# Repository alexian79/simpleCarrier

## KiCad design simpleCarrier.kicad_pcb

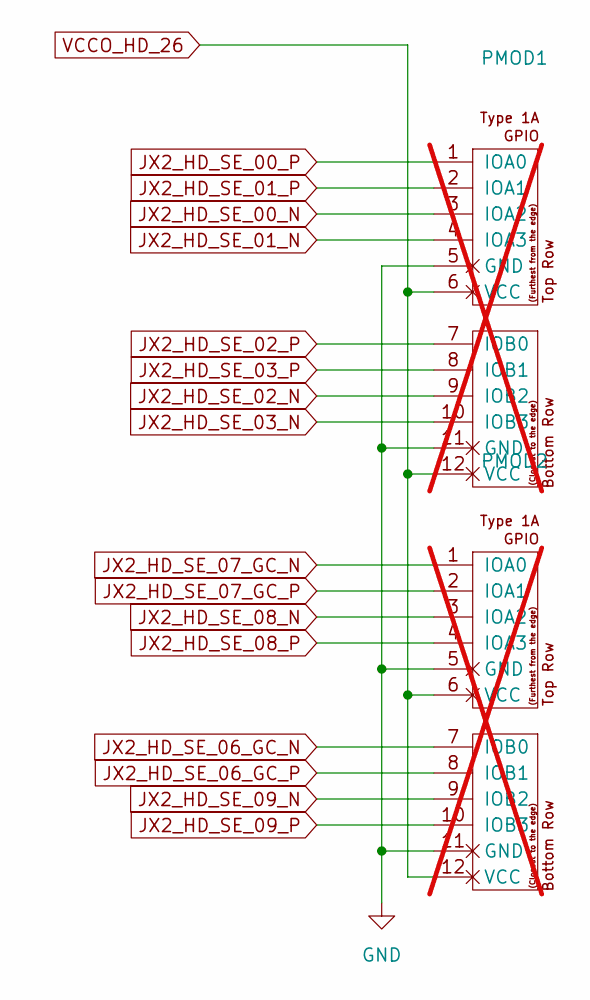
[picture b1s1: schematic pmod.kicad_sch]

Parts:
PMOD1, PMOD2: PMOD-Device-x2-Type-1A-GPIO; pmod_pin_array_6x2; not fitted

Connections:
GND: PMOD1.5 (GND), PMOD1.11 (GND), PMOD2.5 (GND), PMOD2.11 (GND); also elsewhere on the board
JX2_HD_SE_00_N: PMOD1.3 (IOA2); also elsewhere on the board
JX2_HD_SE_00_P: PMOD1.1 (IOA0); also elsewhere on the board
JX2_HD_SE_01_N: PMOD1.4 (IOA3); also elsewhere on the board
JX2_HD_SE_01_P: PMOD1.2 (IOA1); also elsewhere on the board
JX2_HD_SE_02_N: PMOD1.9 (IOB2); also elsewhere on the board
JX2_HD_SE_02_P: PMOD1.7 (IOB0); also elsewhere on the board
JX2_HD_SE_03_N: PMOD1.10 (IOB3); also elsewhere on the board
JX2_HD_SE_03_P: PMOD1.8 (IOB1); also elsewhere on the board
JX2_HD_SE_06_GC_N: PMOD2.7 (IOB0); also elsewhere on the board
JX2_HD_SE_06_GC_P: PMOD2.8 (IOB1); also elsewhere on the board
JX2_HD_SE_07_GC_N: PMOD2.1 (IOA0); also elsewhere on the board
JX2_HD_SE_07_GC_P: PMOD2.2 (IOA1); also elsewhere on the board
JX2_HD_SE_08_N: PMOD2.3 (IOA2); also elsewhere on the board
JX2_HD_SE_08_P: PMOD2.4 (IOA3); also elsewhere on the board
JX2_HD_SE_09_N: PMOD2.9 (IOB2); also elsewhere on the board
JX2_HD_SE_09_P: PMOD2.10 (IOB3); also elsewhere on the board
VCCO_HD_26: PMOD1.6 (VCC), PMOD1.12 (VCC), PMOD2.6 (VCC), PMOD2.12 (VCC); also elsewhere on the board

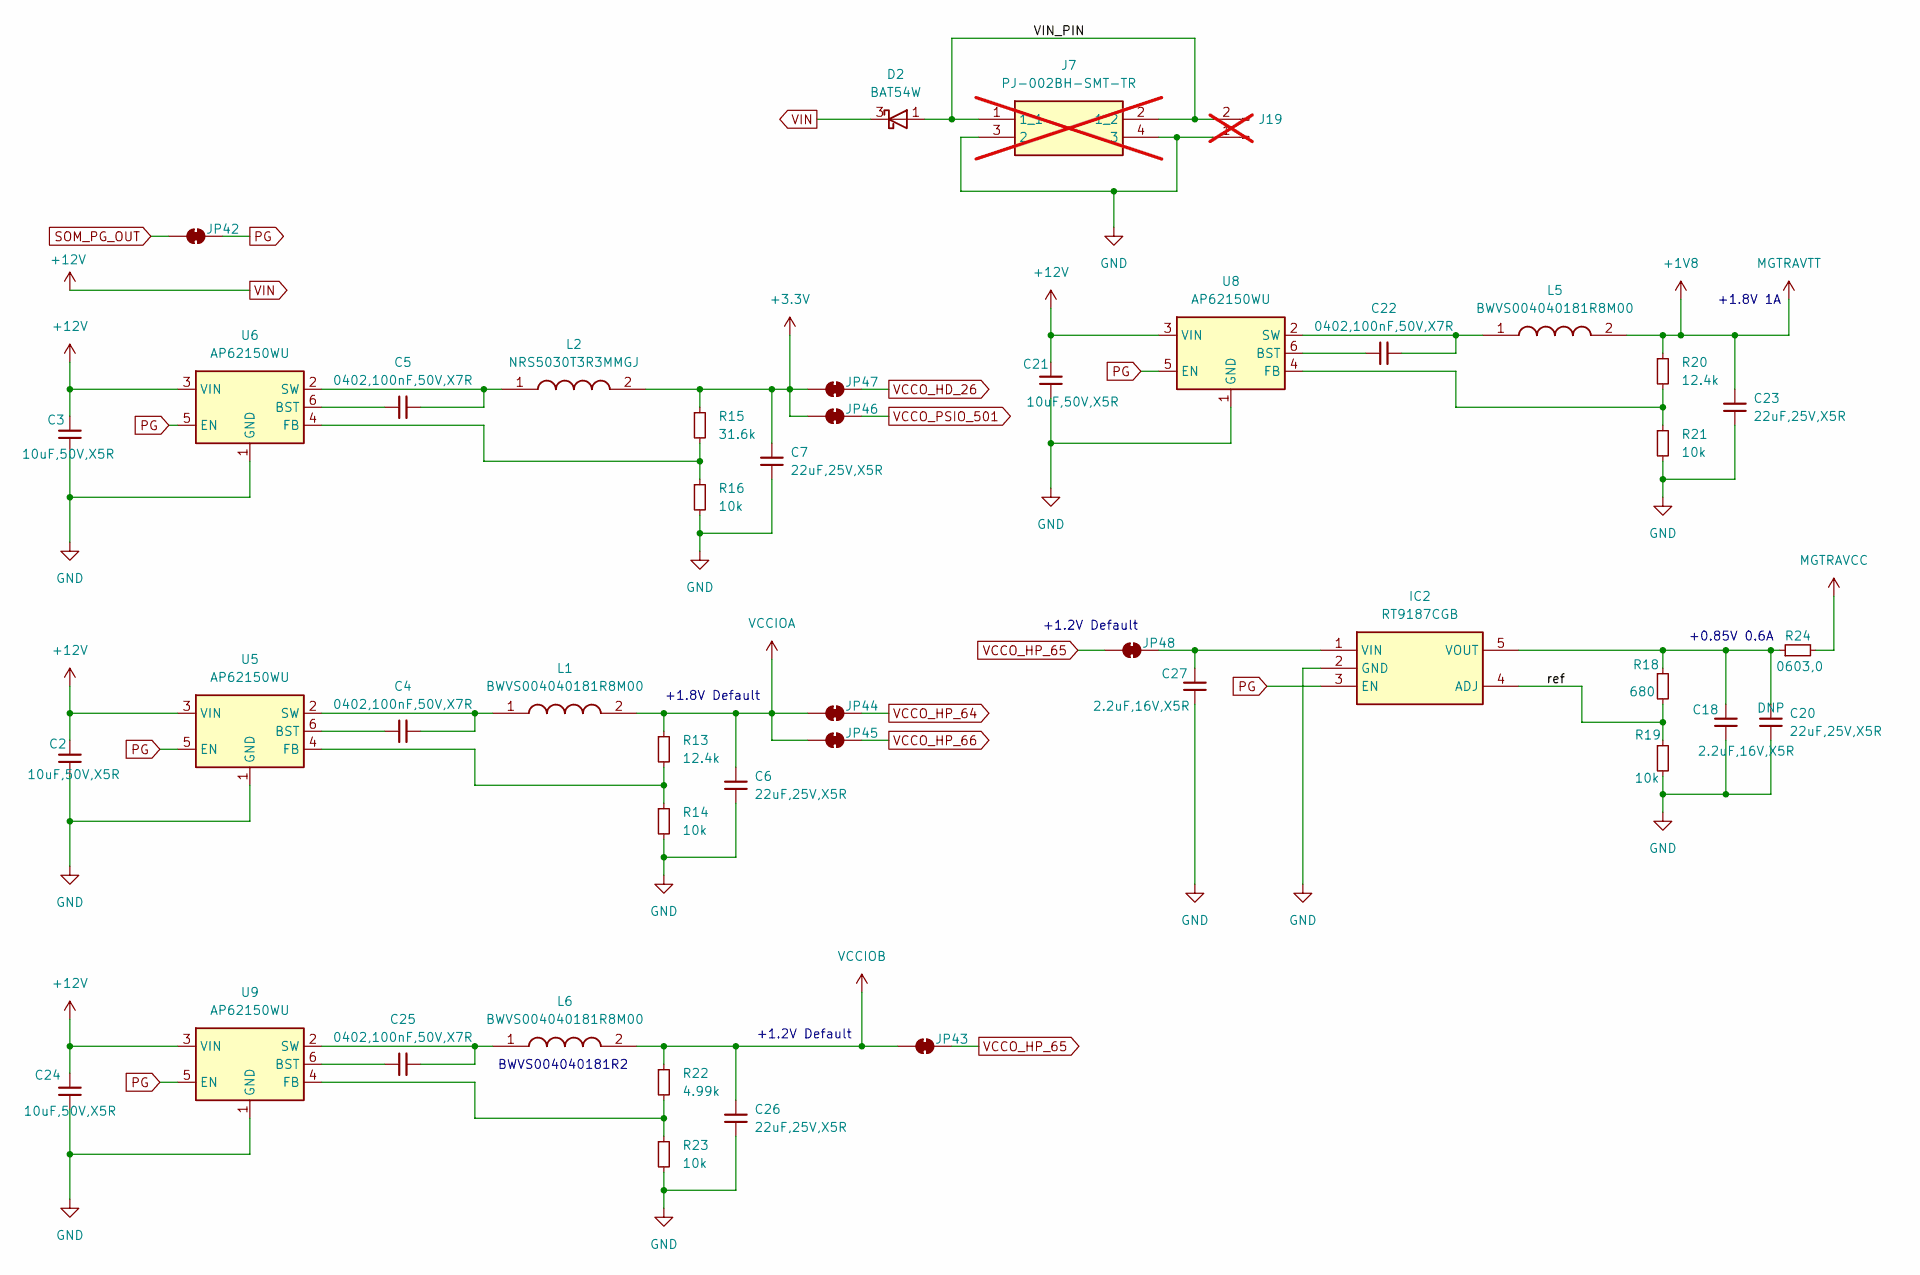
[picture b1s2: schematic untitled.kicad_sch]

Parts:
C2, C3, C21, C24: 10uF,50V,X5R; C_0805_2012Metric; MFGPN GRM21BR61H106KE43L; LCSC C440198
C4, C5, C22, C25: 0402,100nF,50V,X7R; C_0402_1005Metric; MFGPN CL05B104KB54PNC; LCSC C307331
C6, C7, C20, C23, C26: 22uF,25V,X5R; C_0805_2012Metric; MFGPN CL21A226MAQNNNE; LCSC C45783
C18, C27: 2.2uF,16V,X5R; C_0603_1608Metric; MFGPN CL10A225KO8NNNC; LCSC C23630
D2: BAT54W; SOT-323_SC-70
IC2: RT9187CGB; SOT94P279X130-5N; Manufacturer_Part_Number RT9187CGB
J7: PJ-002BH-SMT-TR; PJ002BHSMTTR; Manufacturer_Part_Number PJ-002BH-SMT-TR; Mouser Part Number 490-PJ-002BH-SMT-TR; not fitted
J19: Conn_01x02_Pin; PinHeader_1x02_P2.54mm_Vertical; not fitted
JP42, JP43, JP44, JP45, JP46, JP47, JP48: SolderJumper_2_Bridged; SolderJumper-2_P1.3mm_Bridged_RoundedPad1.0x1.5mm
L1, L5, L6: BWVS004040181R8M00; Manufacturer_Part_Number BWVS004040181R8M00
L2: NRS5030T3R3MMGJ; INDC4949X330N; Manufacturer_Part_Number NRS5030T3R3MMGJ; Mouser Part Number 963-NRS5030T3R3MMGJ
R13, R20: 12.4k; R_0603_1608Metric; MFGPN 0603WAF1202T5E; LCSC C22790
R14, R16, R19, R21, R23: 10k; R_0603_1608Metric; MFGPN 0603WAF1002T5E; LCSC C25804
R15: 31.6k; R_0603_1608Metric; MFGPN 0603WAF3002T5E; LCSC C22984
R18: 680; R_0603_1608Metric; MFGPN 0603WAF6800T5E; LCSC C23228
R22: 4.99k; R_0603_1608Metric; MFGPN 0603WAF1202T5E; LCSC C23046
R24: 0603,0; R_0603_1608Metric; MFGPN 0603WAF0000T5E; LCSC C21189
U5, U6, U8, U9: AP62150WU; TSOT-23-6

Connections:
+1V8: C23.1, L5.2, R20.1; also elsewhere on the board
+3.3V: C7.1, JP46.1 (A), JP47.1 (A), L2.2, R15.1; also elsewhere on the board
/power/VIN_PIN: D2.1 (A), J7.1 (1_1), J7.2 (1_2), J19.2
/power/ref: IC2.4 (ADJ), R18.2, R19.1
GND: C2.2, C3.2, C6.2, C7.2, C18.2, C20.2, C21.2, C23.2, C24.2, C26.2, C27.2, IC2.2 (GND), J7.3 (2), J7.4 (3), J19.1, R14.2, R16.2, R19.2, R21.2, R23.2, U5.1 (GND), U6.1 (GND), U8.1 (GND), U9.1 (GND); also elsewhere on the board
MGTRAVCC: R24.2; also elsewhere on the board
unnamed: C27.1, IC2.1 (VIN), JP48.2 (B)
unnamed: C18.1, C20.1, IC2.5 (VOUT), R18.1, R24.1
unnamed: C4.1, U5.6 (BST)
unnamed: R13.2, R14.1, U5.4 (FB)
unnamed: C4.2, L1.1, U5.2 (SW)
unnamed: C5.1, U6.6 (BST)
unnamed: R15.2, R16.1, U6.4 (FB)
unnamed: C5.2, L2.1, U6.2 (SW)
unnamed: C22.1, U8.6 (BST)
unnamed: R20.2, R21.1, U8.4 (FB)
unnamed: C22.2, L5.1, U8.2 (SW)
unnamed: C25.1, U9.6 (BST)
unnamed: R22.2, R23.1, U9.4 (FB)
unnamed: C25.2, L6.1, U9.2 (SW)
PG: IC2.3 (EN), JP42.2 (B), U5.5 (EN), U6.5 (EN), U8.5 (EN), U9.5 (EN)
SOM_PG_OUT: JP42.1 (A); also elsewhere on the board
VCCIOA: C6.1, JP44.1 (A), JP45.1 (A), L1.2, R13.1
VCCIOB: C26.1, JP43.1 (A), L6.2, R22.1
VCCO_HD_26: JP47.2 (B); also elsewhere on the board
VCCO_HP_64: JP44.2 (B); also elsewhere on the board
VCCO_HP_65: JP43.2 (B), JP48.1 (A); also elsewhere on the board
VCCO_HP_66: JP45.2 (B); also elsewhere on the board
VCCO_PSIO_501: JP46.2 (B); also elsewhere on the board
VIN: C2.1, C3.1, C21.1, C24.1, D2.3 (K), U5.3 (VIN), U6.3 (VIN), U8.3 (VIN), U9.3 (VIN); also elsewhere on the board

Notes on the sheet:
+1.8V Default
+1.8V 1A
+1.2V Default
BWVS004040181R2
+0.85V 0.6A

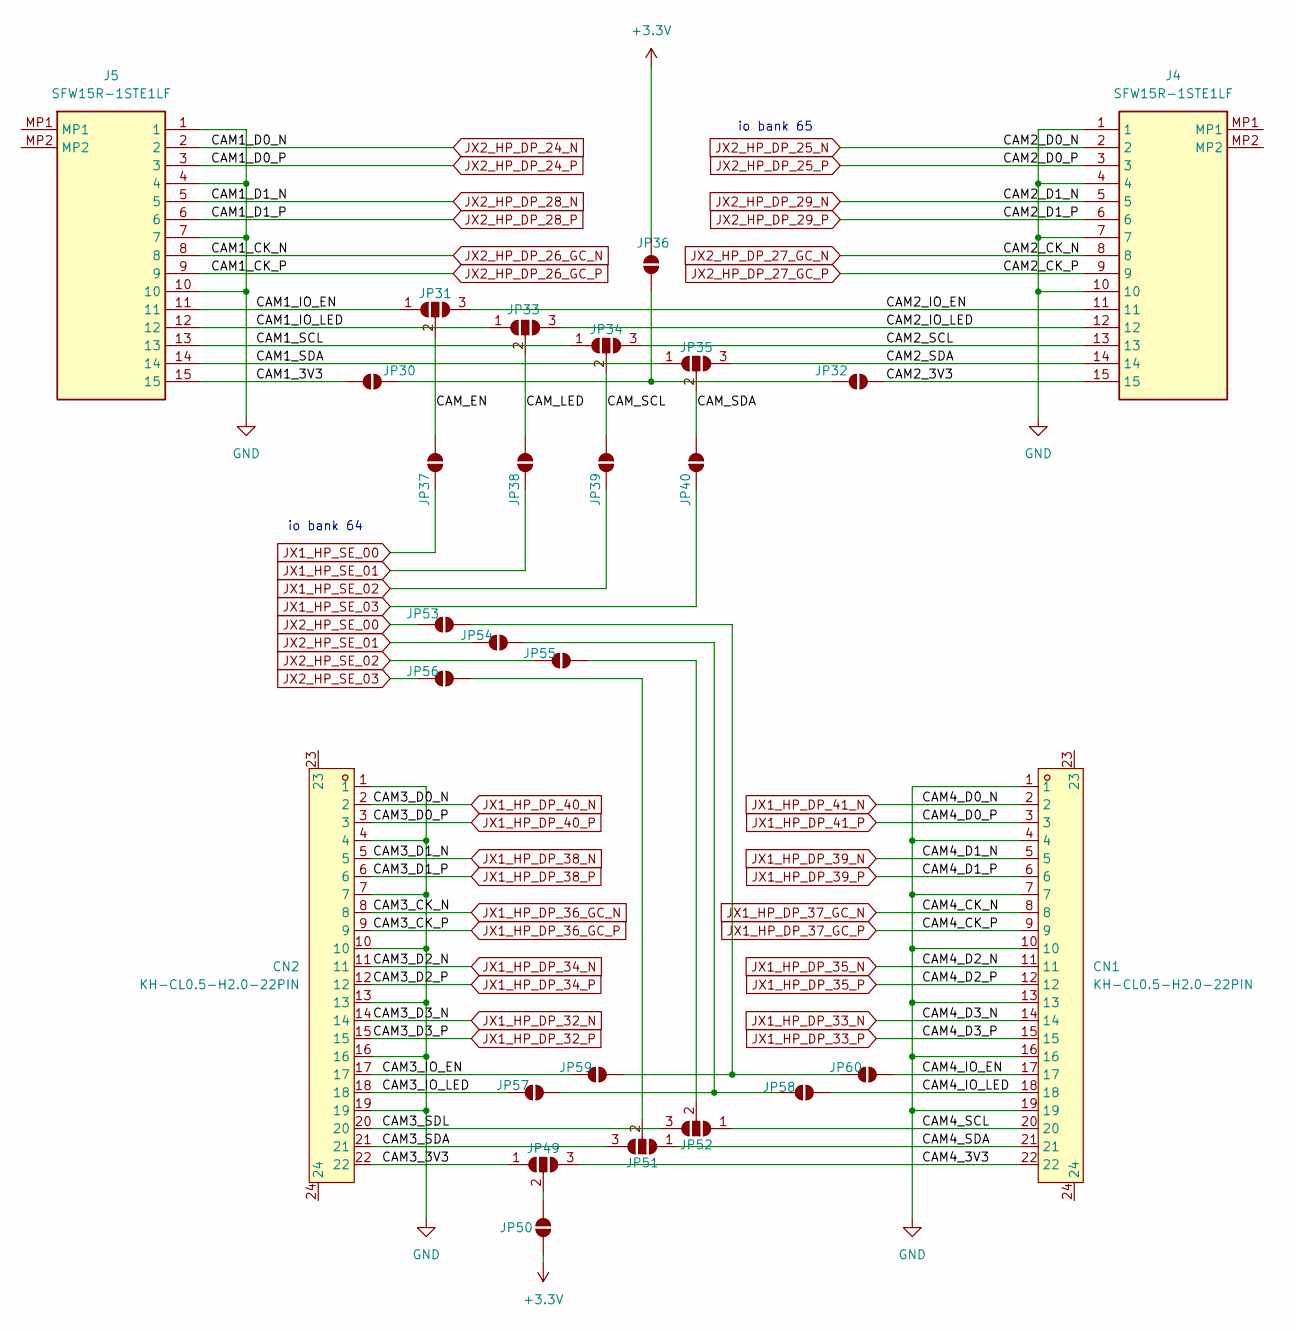
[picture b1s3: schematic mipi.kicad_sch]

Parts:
CN1, CN2: KH-CL0.5-H2.0-22PIN; FPC-SMD_KH-CL0.5-H2.0-22PIN; LCSC Part C2797197
J4, J5: SFW15R-1STE1LF; SFW15R1STE1LF; Manufacturer_Part_Number SFW15R-1STE1LF
JP30, JP32, JP36, JP37, JP38, JP39, JP40, JP50, JP53, JP54, JP55, JP56, JP57, JP58, JP59, JP60: SolderJumper_2_Open; SolderJumper-2_P1.3mm_Open_RoundedPad1.0x1.5mm
JP31, JP33, JP34, JP35, JP49, JP51, JP52: SolderJumper_3_Open; SolderJumper-3_P1.3mm_Open_RoundedPad1.0x1.5mm_NumberLabels

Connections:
+3.3V: JP36.1 (A), JP50.2 (B); also elsewhere on the board
/mipi/CAM1_3V3: J5.15, JP30.1 (A)
/mipi/CAM1_IO_EN: J5.11, JP31.1 (A)
/mipi/CAM1_IO_LED: J5.12, JP33.1 (A)
/mipi/CAM1_SCL: J5.13, JP34.1 (A)
/mipi/CAM1_SDA: J5.14, JP35.1 (A)
/mipi/CAM2_3V3: J4.15, JP32.1 (A)
/mipi/CAM2_IO_EN: J4.11, JP31.3 (B)
/mipi/CAM2_IO_LED: J4.12, JP33.3 (B)
/mipi/CAM2_SCL: J4.13, JP34.3 (B)
/mipi/CAM2_SDA: J4.14, JP35.3 (B)
/mipi/CAM3_3V3: CN2.22, JP49.1 (A)
/mipi/CAM3_IO_EN: CN2.17, JP59.1 (A)
/mipi/CAM3_IO_LED: CN2.18, JP57.1 (A)
/mipi/CAM3_SDA: CN2.21, JP51.3 (B)
/mipi/CAM3_SDL: CN2.20, JP52.3 (B)
/mipi/CAM4_3V3: CN1.22, JP49.3 (B)
/mipi/CAM4_IO_EN: CN1.17, JP60.2 (B)
/mipi/CAM4_IO_LED: CN1.18, JP58.2 (B)
/mipi/CAM4_SCL: CN1.20, JP52.1 (A)
/mipi/CAM4_SDA: CN1.21, JP51.1 (A)
/mipi/CAM_EN: JP31.2 (C), JP37.1 (A)
/mipi/CAM_LED: JP33.2 (C), JP38.1 (A)
/mipi/CAM_SCL: JP34.2 (C), JP39.1 (A)
/mipi/CAM_SDA: JP35.2 (C), JP40.1 (A)
GND: CN1.1, CN1.4, CN1.7, CN1.10, CN1.13, CN1.16, CN1.19, CN2.1, CN2.4, CN2.7, CN2.10, CN2.13, CN2.16, CN2.19, J4.1, J4.4, J4.7, J4.10, J5.1, J5.4, J5.7, J5.10; also elsewhere on the board
JX1_HP_DP_32_N: CN2.14; also elsewhere on the board
JX1_HP_DP_32_P: CN2.15; also elsewhere on the board
JX1_HP_DP_33_N: CN1.14; also elsewhere on the board
JX1_HP_DP_33_P: CN1.15; also elsewhere on the board
JX1_HP_DP_34_N: CN2.11; also elsewhere on the board
JX1_HP_DP_34_P: CN2.12; also elsewhere on the board
JX1_HP_DP_35_N: CN1.11; also elsewhere on the board
JX1_HP_DP_35_P: CN1.12; also elsewhere on the board
JX1_HP_DP_36_GC_N: CN2.8; also elsewhere on the board
JX1_HP_DP_36_GC_P: CN2.9; also elsewhere on the board
JX1_HP_DP_37_GC_N: CN1.8; also elsewhere on the board
JX1_HP_DP_37_GC_P: CN1.9; also elsewhere on the board
JX1_HP_DP_38_N: CN2.5; also elsewhere on the board
JX1_HP_DP_38_P: CN2.6; also elsewhere on the board
JX1_HP_DP_39_N: CN1.5; also elsewhere on the board
JX1_HP_DP_39_P: CN1.6; also elsewhere on the board
JX1_HP_DP_40_N: CN2.2; also elsewhere on the board
JX1_HP_DP_40_P: CN2.3; also elsewhere on the board
JX1_HP_DP_41_N: CN1.2; also elsewhere on the board
JX1_HP_DP_41_P: CN1.3; also elsewhere on the board
JX1_HP_SE_00: JP37.2 (B); also elsewhere on the board
JX1_HP_SE_01: JP38.2 (B); also elsewhere on the board
JX1_HP_SE_02: JP39.2 (B); also elsewhere on the board
JX1_HP_SE_03: JP40.2 (B); also elsewhere on the board
JX2_HP_DP_24_N: J5.2; also elsewhere on the board
JX2_HP_DP_24_P: J5.3; also elsewhere on the board
JX2_HP_DP_25_N: J4.2; also elsewhere on the board
JX2_HP_DP_25_P: J4.3; also elsewhere on the board
JX2_HP_DP_26_GC_N: J5.8; also elsewhere on the board
JX2_HP_DP_26_GC_P: J5.9; also elsewhere on the board
JX2_HP_DP_27_GC_N: J4.8; also elsewhere on the board
JX2_HP_DP_27_GC_P: J4.9; also elsewhere on the board
JX2_HP_DP_28_N: J5.5; also elsewhere on the board
JX2_HP_DP_28_P: J5.6; also elsewhere on the board
JX2_HP_DP_29_N: J4.5; also elsewhere on the board
JX2_HP_DP_29_P: J4.6; also elsewhere on the board
JX2_HP_SE_00: JP53.1 (A); also elsewhere on the board
JX2_HP_SE_01: JP54.1 (A); also elsewhere on the board
JX2_HP_SE_02: JP55.1 (A); also elsewhere on the board
JX2_HP_SE_03: JP56.1 (A); also elsewhere on the board
unnamed: JP30.2 (B), JP32.2 (B), JP36.2 (B)
unnamed: JP49.2 (C), JP50.1 (A)
unnamed: JP51.2 (C), JP56.2 (B)
unnamed: JP52.2 (C), JP55.2 (B)
unnamed: JP53.2 (B), JP59.2 (B), JP60.1 (A)
unnamed: JP54.2 (B), JP57.2 (B), JP58.1 (A)

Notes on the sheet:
io bank 64
io bank 65

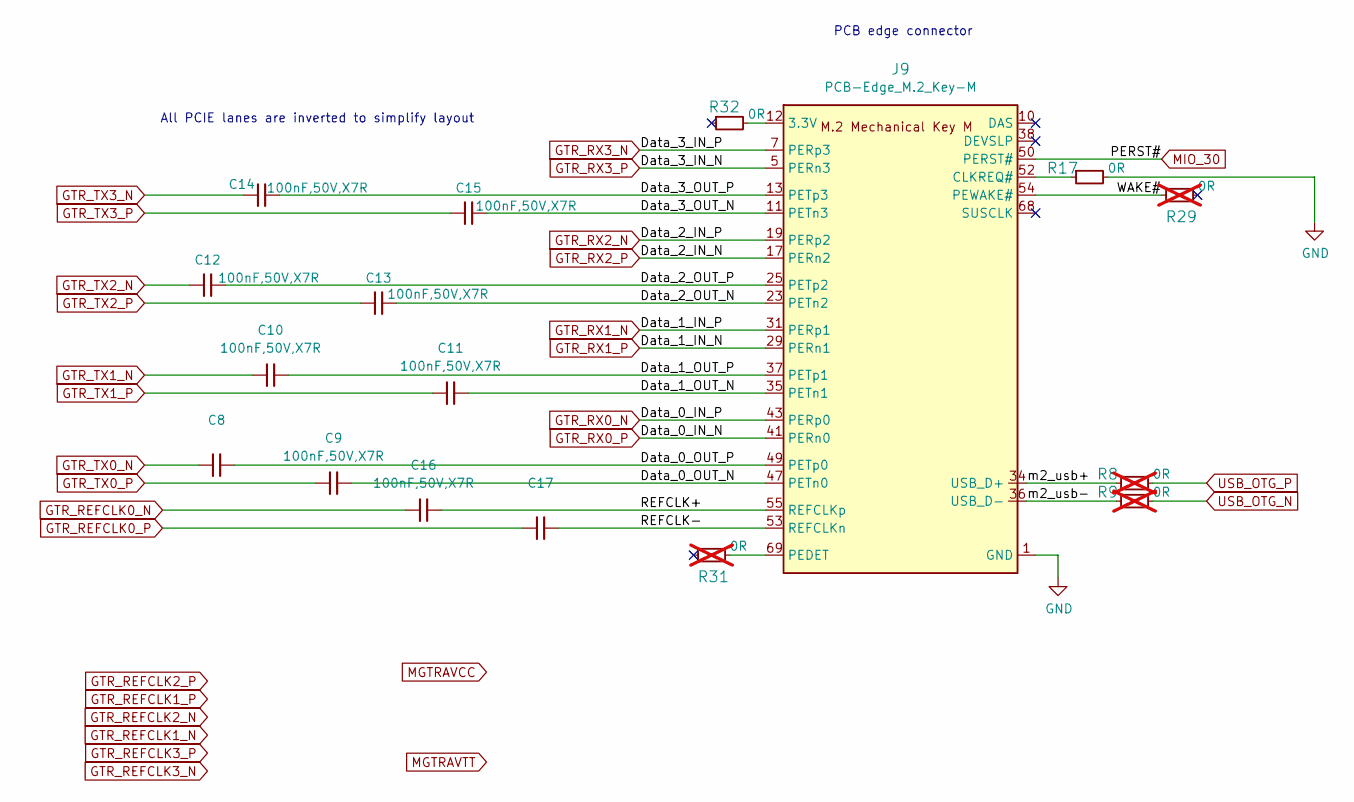
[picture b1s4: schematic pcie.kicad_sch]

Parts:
C8, C9, C10, C11, C12, C13, C14, C15, C16, C17: 100nF,50V,X7R; C_0402_1005Metric; MFGPN CL05B104KO5NNNC; LCSC C1525
J9: PCB-Edge_M.2_Key-M; NGFF_M
R8, R9, R29, R31: R_0R_0402; R_0402_1005Metric_Pad0.72x0.64mm_HandSolder; MPN ERJ2GE0R00X; not fitted
R17, R32: R_0R_0402; R_0402_1005Metric_Pad0.72x0.64mm_HandSolder; MPN ERJ2GE0R00X

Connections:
/PCIE/Data_0_OUT_N: C9.2, J9.47 (PETn0)
/PCIE/Data_0_OUT_P: C8.2, J9.49 (PETp0)
/PCIE/Data_1_OUT_N: C11.2, J9.35 (PETn1)
/PCIE/Data_1_OUT_P: C10.2, J9.37 (PETp1)
/PCIE/Data_2_OUT_N: C13.2, J9.23 (PETn2)
/PCIE/Data_2_OUT_P: C12.2, J9.25 (PETp2)
/PCIE/Data_3_OUT_N: C15.2, J9.11 (PETn3)
/PCIE/Data_3_OUT_P: C14.2, J9.13 (PETp3)
/PCIE/REFCLK+: C16.2, J9.55 (REFCLKp)
/PCIE/REFCLK-: C17.2, J9.53 (REFCLKn)
/PCIE/WAKE#: J9.54 (PEWAKE#), R29.1
/PCIE/m2_usb+: J9.34 (USB_D+), R8.1
/PCIE/m2_usb-: J9.36 (USB_D-), R9.1
GND: J9.1 (GND), J9.3 (GND), J9.9 (GND), J9.15 (GND), J9.21 (GND), J9.27 (GND), J9.33 (GND), J9.39 (GND), J9.45 (GND), J9.51 (GND), J9.57 (GND), J9.71 (GND), J9.73 (GND), J9.75 (GND), R17.2; also elsewhere on the board
GTR_REFCLK0_N: C16.1; also elsewhere on the board
GTR_REFCLK0_P: C17.1; also elsewhere on the board
GTR_RX0_N: J9.43 (PERp0); also elsewhere on the board
GTR_RX0_P: J9.41 (PERn0); also elsewhere on the board
GTR_RX1_N: J9.31 (PERp1); also elsewhere on the board
GTR_RX1_P: J9.29 (PERn1); also elsewhere on the board
GTR_RX2_N: J9.19 (PERp2); also elsewhere on the board
GTR_RX2_P: J9.17 (PERn2); also elsewhere on the board
GTR_RX3_N: J9.7 (PERp3); also elsewhere on the board
GTR_RX3_P: J9.5 (PERn3); also elsewhere on the board
GTR_TX0_N: C8.1; also elsewhere on the board
GTR_TX0_P: C9.1; also elsewhere on the board
GTR_TX1_N: C10.1; also elsewhere on the board
GTR_TX1_P: C11.1; also elsewhere on the board
GTR_TX2_N: C12.1; also elsewhere on the board
GTR_TX2_P: C13.1; also elsewhere on the board
GTR_TX3_N: C14.1; also elsewhere on the board
GTR_TX3_P: C15.1; also elsewhere on the board
MIO_30: J9.50 (PERST#); also elsewhere on the board
unnamed: J9.2 (3.3V), J9.4 (3.3V), J9.12 (3.3V), J9.14 (3.3V), J9.16 (3.3V), J9.18 (3.3V), J9.70 (3.3V), J9.72 (3.3V), J9.74 (3.3V), R32.2
unnamed: J9.52 (CLKREQ#), R17.1
unnamed: J9.69 (PEDET), R31.2
USB_OTG_N: R9.2; also elsewhere on the board
USB_OTG_P: R8.2; also elsewhere on the board

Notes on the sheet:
PCB edge connector
All PCIE lanes are inverted to simplify layout

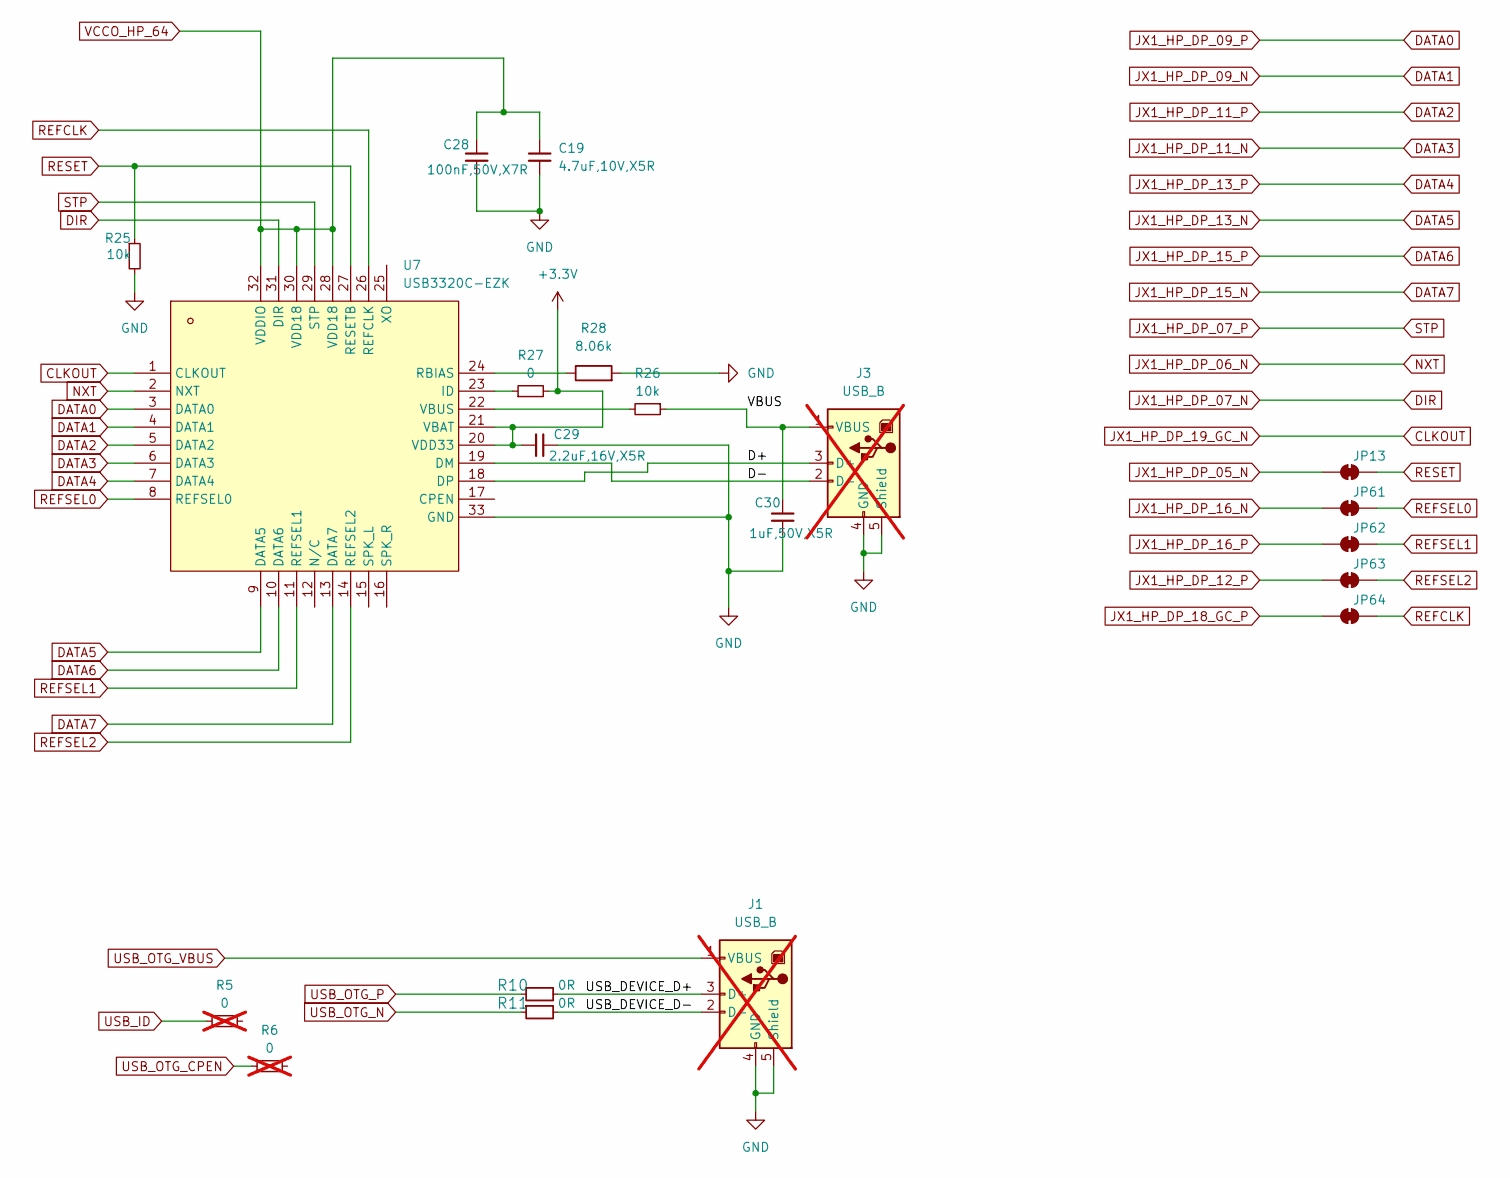
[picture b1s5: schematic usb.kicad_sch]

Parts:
C19: 4.7uF,10V,X5R; C_0402_1005Metric; MFGPN CL05A475MP5NRNC; LCSC C23733
C28: 100nF,50V,X7R; C_0603_1608Metric; MFGPN CC0603KRX7R9BB104; LCSC C14663
C29: 2.2uF,16V,X5R; C_0603_1608Metric; MFGPN CL10A225KO8NNNC; LCSC C23630
C30: 1uF,50V,X5R; C_0603_1608Metric; MFGPN CL10A105KB8NNNC; LCSC C15849
J1, J3: USB_B; USB_B_OST_USB-B1HSxx_Horizontal; not fitted
JP13, JP61, JP62, JP63, JP64: SolderJumper_2_Bridged; SolderJumper-2_P1.3mm_Bridged_RoundedPad1.0x1.5mm
R5, R6: 0; R_0402_1005Metric; MFGPN 0402WGF0000TCE; LCSC C17168; not fitted
R10, R11: R_0R_0402; R_0402_1005Metric_Pad0.72x0.64mm_HandSolder; MPN ERJ2GE0R00X
R25, R26: 10k; R_0603_1608Metric; MFGPN 0603WAF1002T5E; LCSC C25804
R27: 0; R_0402_1005Metric; MFGPN 0402WGF0000TCE; LCSC C17168
R28: 8.06k; R_0402_1005Metric
U7: USB3320C-EZK; QFN-32_L5.0-W5.0-P0.50-BL-EP3.4; LCSC Part C52447

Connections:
+3.3V: C29.1, R27.2, U7.20 (VDD33), U7.21 (VBAT); also elsewhere on the board
/usb/D+: J3.3 (D+), U7.18 (DP)
/usb/D-: J3.2 (D-), U7.19 (DM)
/usb/USB_DEVICE_D+: J1.3 (D+), R10.2
/usb/USB_DEVICE_D-: J1.2 (D-), R11.2
/usb/VBUS: C30.1, J3.1 (VBUS), R26.1
CLKOUT: U7.1 (CLKOUT); also elsewhere on the board
DATA0: U7.3 (DATA0); also elsewhere on the board
DATA1: U7.4 (DATA1); also elsewhere on the board
DATA2: U7.5 (DATA2); also elsewhere on the board
DATA3: U7.6 (DATA3); also elsewhere on the board
DATA4: U7.7 (DATA4); also elsewhere on the board
DATA5: U7.9 (DATA5); also elsewhere on the board
DATA6: U7.10 (DATA6); also elsewhere on the board
DATA7: U7.13 (DATA7); also elsewhere on the board
DIR: U7.31 (DIR); also elsewhere on the board
GND: C19.2, C28.2, C29.2, C30.2, J1.4 (GND), J1.5 (Shield), J3.4 (GND), J3.5 (Shield), R25.2, R28.2, U7.33 (GND); also elsewhere on the board
JX1_HP_DP_05_N: JP13.1 (A); also elsewhere on the board
JX1_HP_DP_06_N: U7.2 (NXT); also elsewhere on the board
JX1_HP_DP_07_P: U7.29 (STP); also elsewhere on the board
JX1_HP_DP_12_P: JP63.1 (A); also elsewhere on the board
JX1_HP_DP_16_N: JP61.1 (A); also elsewhere on the board
JX1_HP_DP_16_P: JP62.1 (A); also elsewhere on the board
JX1_HP_DP_18_GC_P: JP64.1 (A); also elsewhere on the board
unnamed: R27.1, U7.23 (ID)
unnamed: R28.1, U7.24 (RBIAS)
unnamed: R26.2, U7.22 (VBUS)
REFCLK: JP64.2 (B), U7.26 (REFCLK)
REFSEL0: JP61.2 (B), U7.8 (REFSEL0)
REFSEL1: JP62.2 (B), U7.11 (REFSEL1)
REFSEL2: JP63.2 (B), U7.14 (REFSEL2)
RESET: JP13.2 (B), R25.1, U7.27 (RESETB)
USB_ID: R5.1; also elsewhere on the board
USB_OTG_CPEN: R6.1; also elsewhere on the board
USB_OTG_N: R11.1; also elsewhere on the board
USB_OTG_P: R10.1; also elsewhere on the board
USB_OTG_VBUS: J1.1 (VBUS); also elsewhere on the board
VCCO_HP_64: C19.1, C28.1, U7.28 (VDD18), U7.30 (VDD18), U7.32 (VDDIO); also elsewhere on the board

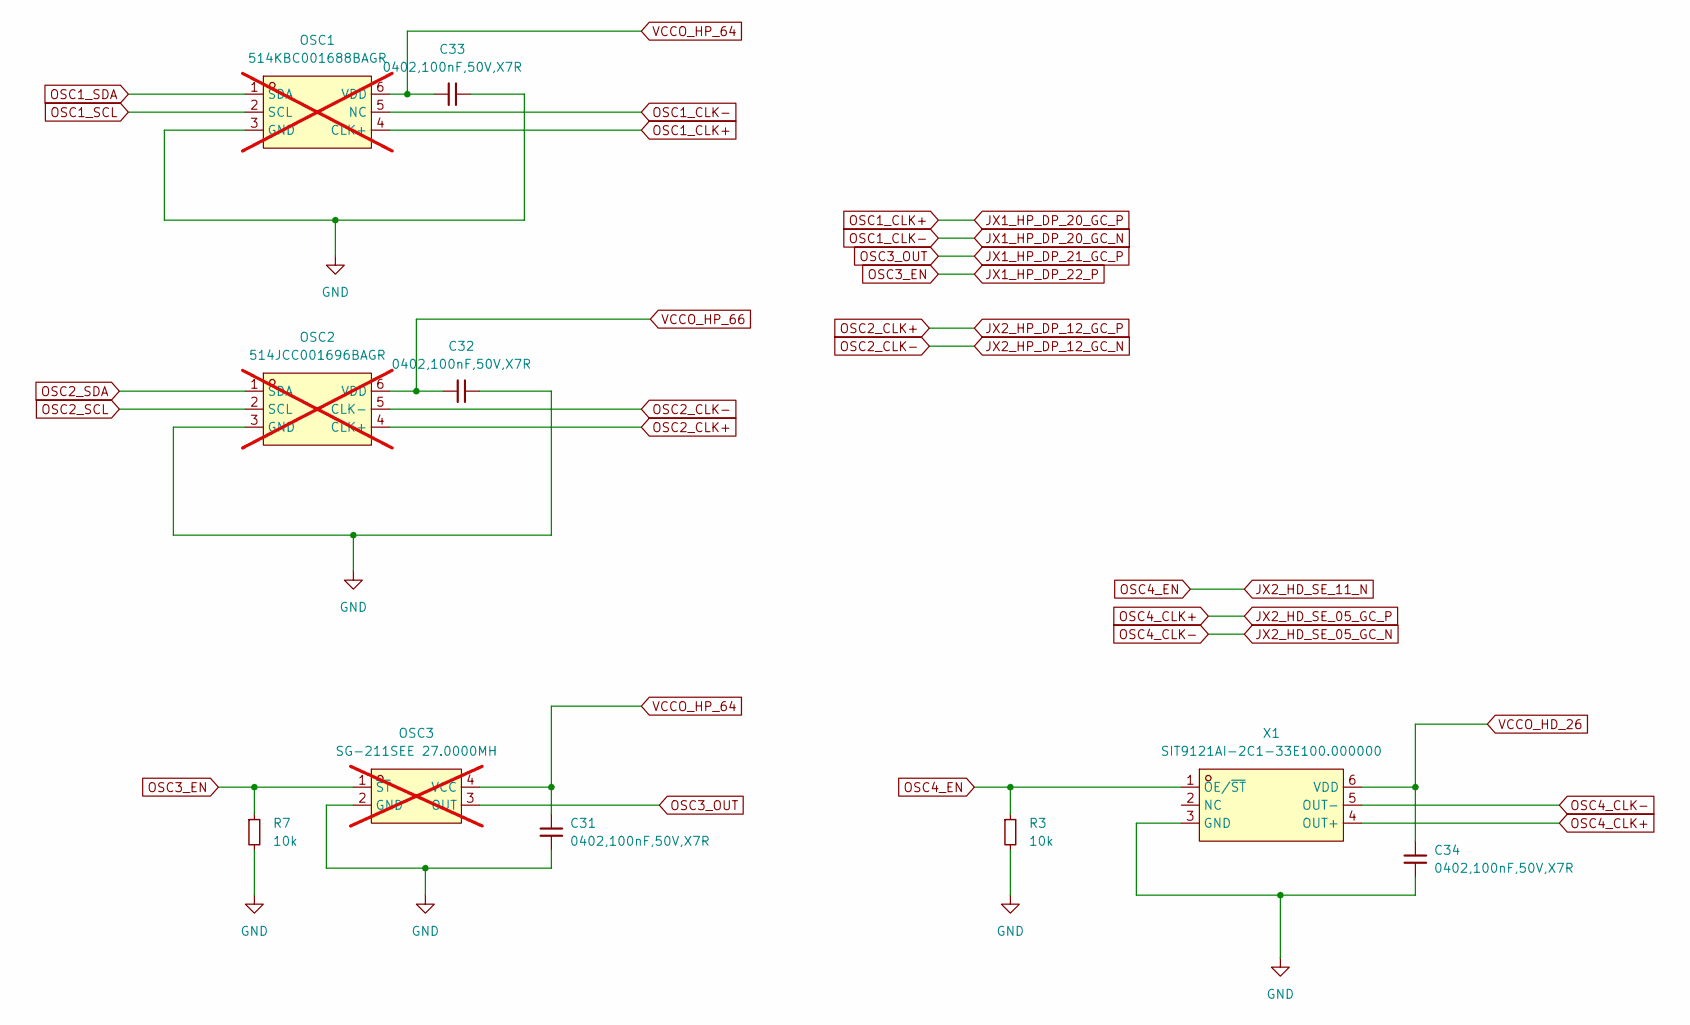
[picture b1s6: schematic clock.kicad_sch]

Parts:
C31, C32, C33, C34: 0402,100nF,50V,X7R; C_0402_1005Metric; MFGPN CL05B104KB54PNC; LCSC C307331
OSC1: 514KBC001688BAGR; OSC-SMD_6P-L5.0-W3.2-BL-A; LCSC Part C2022642; not fitted
OSC2: 514JCC001696BAGR; OSC-SMD_6P-L5.0-W3.2-BL-A; LCSC Part C2021532; not fitted
OSC3: SG-211SEE 27.0000MH; OSC-SMD_4P-L2.5-W2.0-BL_CTS_CA25; LCSC Part C1674985; not fitted
R3, R7: 10k; R_0402_1005Metric; MFGPN 0402WGF1002TCE; LCSC C25744
X1: SIT9121AI-2C1-33E100.000000; OSC-SMD_6P-L5.0-W3.2-BL-A; LCSC Part C401165

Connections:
GND: C31.2, C32.2, C33.2, C34.2, OSC1.3 (GND), OSC2.3 (GND), OSC3.2 (GND), R3.2, R7.2, X1.3 (GND); also elsewhere on the board
JX1_HP_DP_20_GC_N: OSC1.5 (NC); also elsewhere on the board
JX1_HP_DP_20_GC_P: OSC1.4 (CLK+); also elsewhere on the board
JX1_HP_DP_21_GC_P: OSC3.3 (OUT); also elsewhere on the board
JX1_HP_DP_22_P: OSC3.1 (~ST), R7.1; also elsewhere on the board
JX2_HD_SE_05_GC_N: X1.5 (OUT-); also elsewhere on the board
JX2_HD_SE_05_GC_P: X1.4 (OUT+); also elsewhere on the board
JX2_HD_SE_11_N: R3.1, X1.1 (OE/~ST); also elsewhere on the board
JX2_HP_DP_12_GC_N: OSC2.5 (CLK-); also elsewhere on the board
JX2_HP_DP_12_GC_P: OSC2.4 (CLK+); also elsewhere on the board
OSC1_SCL: OSC1.2 (SCL)
OSC1_SDA: OSC1.1 (SDA)
OSC2_SCL: OSC2.2 (SCL)
OSC2_SDA: OSC2.1 (SDA)
VCCO_HD_26: C34.1, X1.6 (VDD); also elsewhere on the board
VCCO_HP_64: C31.1, C33.1, OSC1.6 (VDD), OSC3.4 (VCC); also elsewhere on the board
VCCO_HP_66: C32.1, OSC2.6 (VDD); also elsewhere on the board

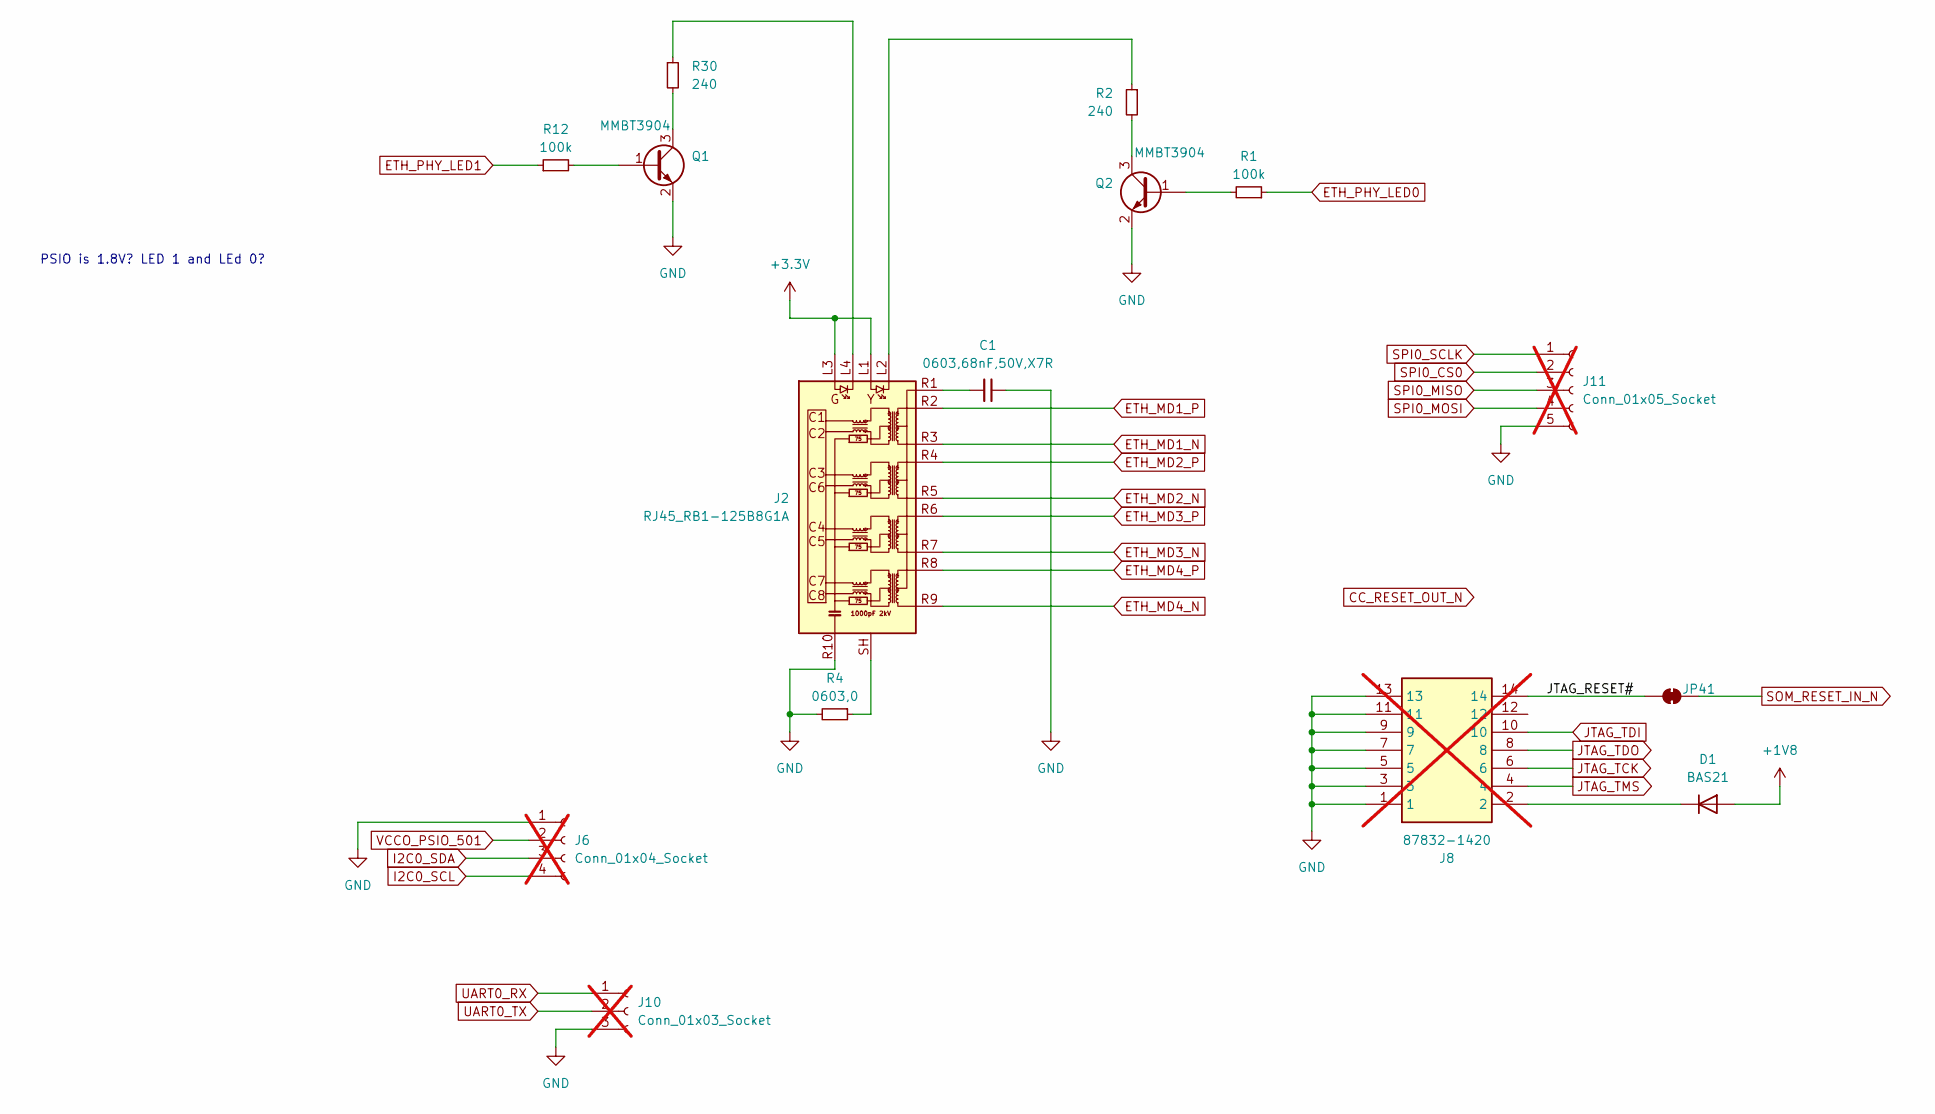
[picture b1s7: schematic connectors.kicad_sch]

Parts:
C1: 0603,68nF,50V,X7R; C_0603_1608Metric; MFGPN CL10B683KB8NNNC; LCSC C31658
D1: BAS21; SOT-23
J2: RJ45_RB1-125B8G1A; RJ45_UDE_RB1-125B8G1A
J6: Conn_01x04_Socket; JST_SH_BM04B-SRSS-TB_1x04-1MP_P1.00mm_Vertical; not fitted
J8: 87832-1420; Manufacturer_Part_Number 87832-1420; Mouser Part Number 538-87832-1420; not fitted
J10: Conn_01x03_Socket; JST_SH_BM03B-SRSS-TB_1x03-1MP_P1.00mm_Vertical; not fitted
J11: Conn_01x05_Socket; JST_SH_BM05B-SRSS-TB_1x05-1MP_P1.00mm_Vertical; not fitted
JP41: SolderJumper_2_Bridged; SolderJumper-2_P1.3mm_Bridged_RoundedPad1.0x1.5mm
Q1, Q2: MMBT3904; SOT-23
R1, R12: 100k; R_0402_1005Metric; MFGPN 0402WGF1003TCE; LCSC C25741
R2, R30: 240; R_0603_1608Metric; MFGPN 0603WAF2400T5E; LCSC C23350
R4: 0603,0; R_0603_1608Metric; MFGPN 0603WAF0000T5E; LCSC C21189

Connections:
+1V8: D1.1 (A); also elsewhere on the board
+3.3V: J2.L1, J2.L3; also elsewhere on the board
/connectors/JTAG_RESET#: J8.14, JP41.1 (A)
ETH_MD1_N: J2.R3 (TD1-); also elsewhere on the board
ETH_MD1_P: J2.R2 (TD1+); also elsewhere on the board
ETH_MD2_N: J2.R5 (TD2-); also elsewhere on the board
ETH_MD2_P: J2.R4 (TD2+); also elsewhere on the board
ETH_MD3_N: J2.R7 (TD3-); also elsewhere on the board
ETH_MD3_P: J2.R6 (TD3+); also elsewhere on the board
ETH_MD4_N: J2.R9 (TD4-); also elsewhere on the board
ETH_MD4_P: J2.R8 (TD4+); also elsewhere on the board
ETH_PHY_LED0: R1.1; also elsewhere on the board
ETH_PHY_LED1: R12.1; also elsewhere on the board
GND: C1.2, J2.R10 (GND), J6.1, J8.1, J8.3, J8.5, J8.7, J8.9, J8.11, J8.13, J10.3, J11.5, Q1.2 (E), Q2.2 (E), R4.2; also elsewhere on the board
I2C0_SCL: J6.4; also elsewhere on the board
I2C0_SDA: J6.3; also elsewhere on the board
JTAG_TCK: J8.6; also elsewhere on the board
JTAG_TDI: J8.10; also elsewhere on the board
JTAG_TDO: J8.8; also elsewhere on the board
JTAG_TMS: J8.4; also elsewhere on the board
MIO_38: J11.1; also elsewhere on the board
MIO_41: J11.2; also elsewhere on the board
MIO_42: J11.3; also elsewhere on the board
MIO_43: J11.4; also elsewhere on the board
MIO_46: J10.1; also elsewhere on the board
MIO_47: J10.2; also elsewhere on the board
unnamed: D1.3 (K), J8.2
unnamed: C1.1, J2.R1 (CT)
unnamed: J2.L2, R2.1
unnamed: J2.L4, R30.1
unnamed: J2.SH, R4.1
unnamed: Q1.1 (B), R12.2
unnamed: Q1.3 (C), R30.2
unnamed: Q2.1 (B), R1.2
unnamed: Q2.3 (C), R2.2
SOM_RESET_IN_N: JP41.2 (B); also elsewhere on the board
VCCO_PSIO_501: J6.2; also elsewhere on the board

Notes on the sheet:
PSIO is 1.8V? LED 1 and LEd 0?

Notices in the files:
parts and their libraries:
License: Apache-2.0
